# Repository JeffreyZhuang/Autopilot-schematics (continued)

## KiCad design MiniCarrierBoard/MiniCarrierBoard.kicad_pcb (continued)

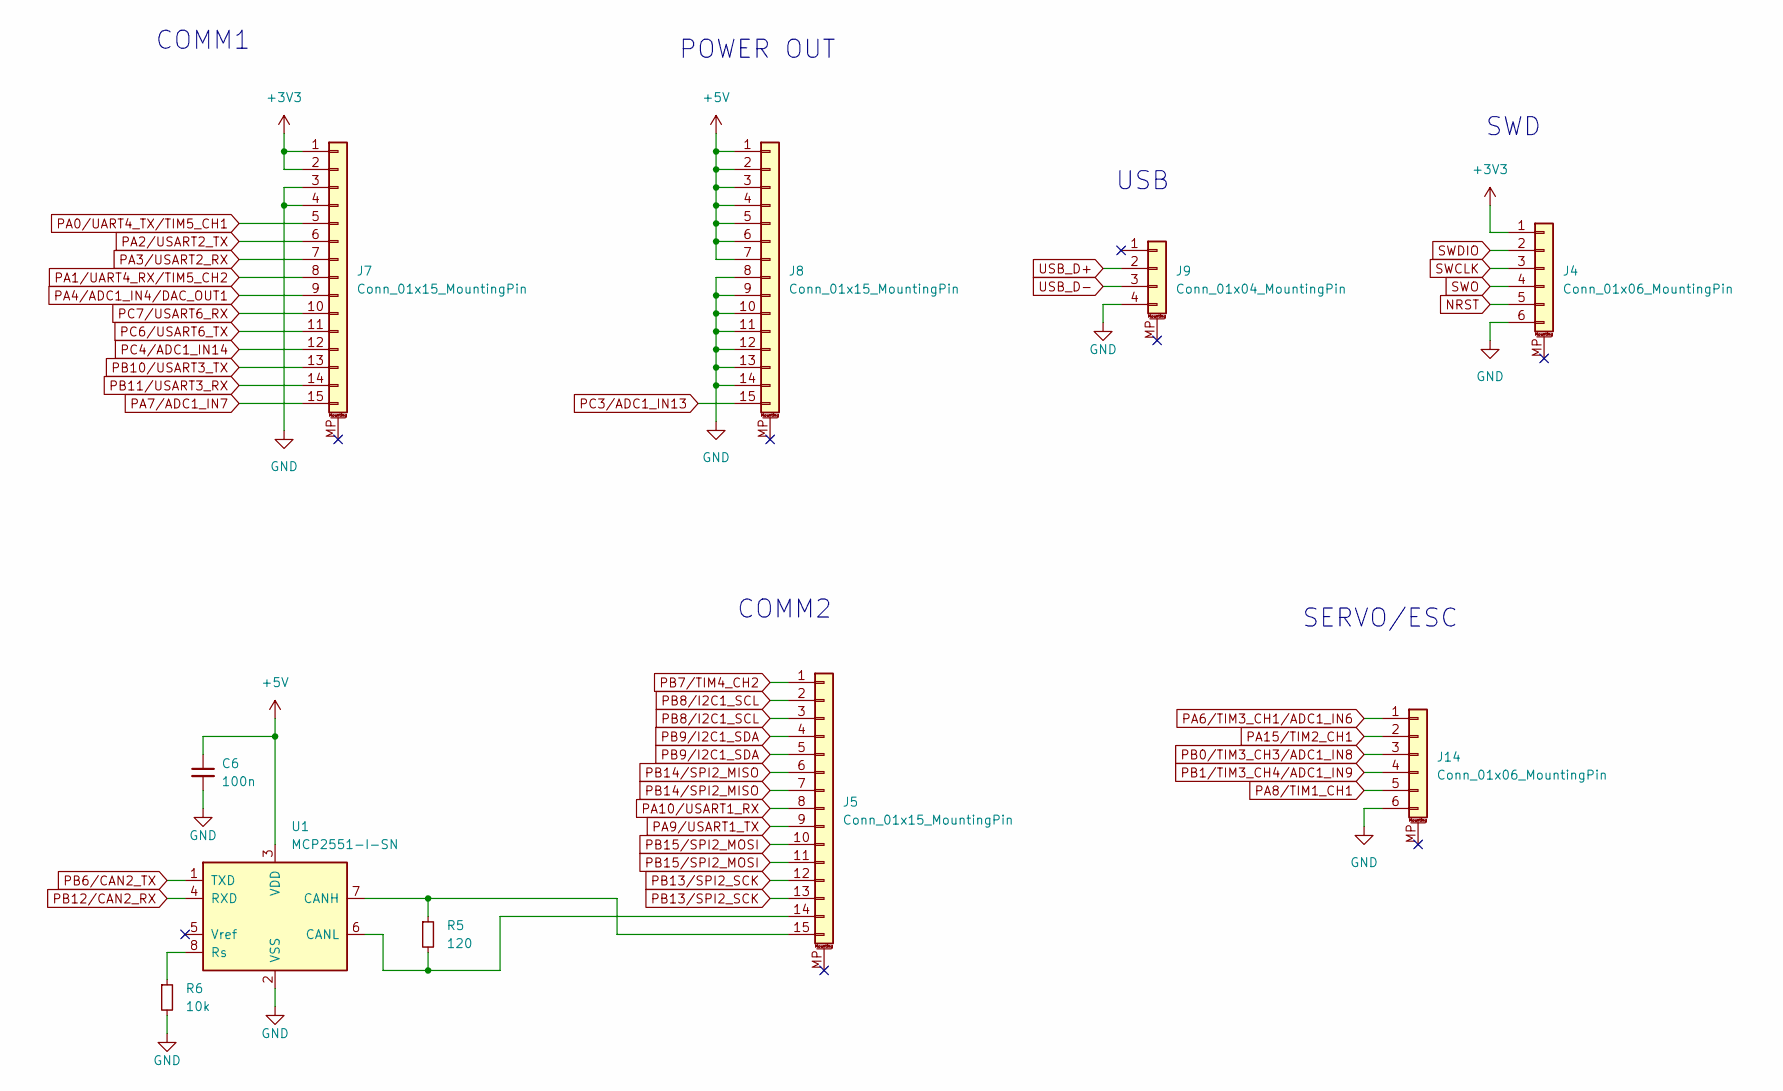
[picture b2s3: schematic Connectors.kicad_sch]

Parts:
C6: 100n; C_0402_1005Metric_Pad0.74x0.62mm_HandSolder; LCSC Part # N/A (C1525)
J4, J14: Conn_01x06_MountingPin; JST_GH_BM06B-GHS-TBT_1x06-1MP_P1.25mm_Vertical; LCSC Part # C189892
J5, J7, J8: Conn_01x15_MountingPin; JST_GH_BM15B-GHS-TBT_1x15-1MP_P1.25mm_Vertical; LCSC Part # C5305069
J9: Conn_01x04_MountingPin; JST_GH_BM04B-GHS-TBT_1x04-1MP_P1.25mm_Vertical; LCSC Part # C161692
R5: 120; R_0402_1005Metric_Pad0.72x0.64mm_HandSolder; LCSC Part # C25079
R6: 10k; R_0402_1005Metric_Pad0.72x0.64mm_HandSolder; LCSC Part # N/A (C25744)
U1: MCP2551-I-SN; SOIC-8_3.9x4.9mm_P1.27mm; LCSC Part # C49558

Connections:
+3V3: J4.1, J7.1, J7.2; also elsewhere on the board
+5V: C6.1, J8.1, J8.2, J8.3, J8.4, J8.5, J8.6, J8.7, U1.3 (VDD); also elsewhere on the board
GND: C6.2, J4.6, J7.3, J7.4, J8.8, J8.9, J8.10, J8.11, J8.12, J8.13, J8.14, J9.4, J14.6, R6.2, U1.2 (VSS); also elsewhere on the board
NRST: J4.5; also elsewhere on the board
unnamed: J5.14, R5.2, U1.6 (CANL)
unnamed: J5.15, R5.1, U1.7 (CANH)
unnamed: R6.1, U1.8 (Rs)
PA0/UART4_TX/TIM5_CH1: J7.5; also elsewhere on the board
PA1/UART4_RX/TIM5_CH2: J7.8; also elsewhere on the board
PA2/USART2_TX: J7.6; also elsewhere on the board
PA3/USART2_RX: J7.7; also elsewhere on the board
PA4/ADC1_IN4/DAC_OUT1: J7.9; also elsewhere on the board
PA6/TIM3_CH1/ADC1_IN6: J14.1; also elsewhere on the board
PA7/ADC1_IN7: J7.15; also elsewhere on the board
PA8/TIM1_CH1: J14.5; also elsewhere on the board
PA9/USART1_TX: J5.9; also elsewhere on the board
PA10/USART1_RX: J5.8; also elsewhere on the board
PA15/TIM2_CH1: J14.2; also elsewhere on the board
PB0/TIM3_CH3/ADC1_IN8: J14.3; also elsewhere on the board
PB1/TIM3_CH4/ADC1_IN9: J14.4; also elsewhere on the board
PB6/CAN2_TX: U1.1 (TXD); also elsewhere on the board
PB7/TIM4_CH2: J5.1; also elsewhere on the board
PB8/I2C1_SCL: J5.2, J5.3; also elsewhere on the board
PB9/I2C1_SDA: J5.4, J5.5; also elsewhere on the board
PB10/USART3_TX: J7.13; also elsewhere on the board
PB11/USART3_RX: J7.14; also elsewhere on the board
PB12/CAN2_RX: U1.4 (RXD); also elsewhere on the board
PB13/SPI2_SCK: J5.12, J5.13; also elsewhere on the board
PB14/SPI2_MISO: J5.6, J5.7; also elsewhere on the board
PB15/SPI2_MOSI: J5.10, J5.11; also elsewhere on the board
PC3/ADC1_IN13: J8.15; also elsewhere on the board
PC4/ADC1_IN14: J7.12; also elsewhere on the board
PC6/USART6_TX: J7.11; also elsewhere on the board
PC7/USART6_RX: J7.10; also elsewhere on the board
SWCLK: J4.3; also elsewhere on the board
SWDIO: J4.2; also elsewhere on the board
SWO: J4.4; also elsewhere on the board
USB_D+: J9.2; also elsewhere on the board
USB_D-: J9.3; also elsewhere on the board

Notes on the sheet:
POWER OUT
COMM1
SWD
USB
COMM2
SERVO/ESC

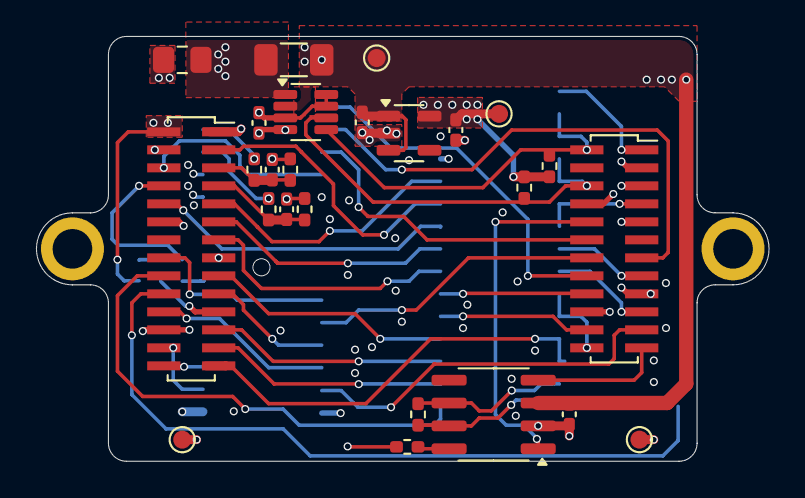
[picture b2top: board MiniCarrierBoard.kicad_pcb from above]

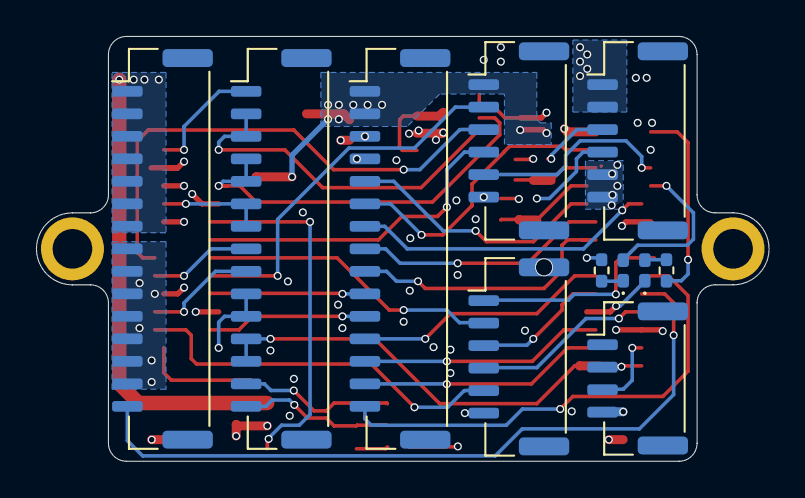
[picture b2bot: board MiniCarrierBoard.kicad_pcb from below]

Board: 4 copper layers, 40.7 x 23.6 mm, 38 parts (11 on the bottom side), 47 nets.

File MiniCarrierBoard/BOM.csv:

"Reference","Value","Footprint","Qty","LCSC Part #"
"C1,C2","1u","Capacitor_SMD:C_0402_1005Metric_Pad0.74x0.62mm_HandSolder","2","N/A (C2959727)"
"C3,C6,C9,C10","100n","Capacitor_SMD:C_0402_1005Metric_Pad0.74x0.62mm_HandSolder","4","N/A (C1525)"
"C5","10u","Capacitor_SMD:C_0805_2012Metric_Pad1.18x1.45mm_HandSolder","1","N/A (C15850)"
"D1","GREEN","LED_SMD:LED_0402_1005Metric_Pad0.77x0.64mm_HandSolder","1","C130723"
"D2","RED","LED_SMD:LED_0402_1005Metric_Pad0.77x0.64mm_HandSolder","1","N/A (C130719)"
"H1,H2","MountingHole_Pad","MountingHole:MountingHole_2.2mm_M2_ISO7380_Pad","2","N/A"
"J1","Conn_02x12_Odd_Even","Connector_PinSocket_1.00mm:PinSocket_2x12_P1.00mm_Vertical_SMD","1","N/A"
"J2","Conn_02x14_Odd_Even","Connector_PinSocket_1.00mm:PinSocket_2x14_P1.00mm_Vertical_SMD","1","N/A"
"J4,J6,J14","Conn_01x06_MountingPin","Connector_JST:JST_GH_BM06B-GHS-TBT_1x06-1MP_P1.25mm_Vertical","3","C189892"
"J5,J7,J8","Conn_01x15_MountingPin","Connector_JST:JST_GH_BM15B-GHS-TBT_1x15-1MP_P1.25mm_Vertical","3","C5305069"
"J9","Conn_01x04_MountingPin","Connector_JST:JST_GH_BM04B-GHS-TBT_1x04-1MP_P1.25mm_Vertical","1","C161692"
"R1,R2","1k","Resistor_SMD:R_0402_1005Metric_Pad0.72x0.64mm_HandSolder","2","N/A (C11702)"
"R3,R4","2k2","Resistor_SMD:R_0402_1005Metric_Pad0.72x0.64mm_HandSolder","2","N/A (C25879)"
"R5","120","Resistor_SMD:R_0402_1005Metric_Pad0.72x0.64mm_HandSolder","1","C25079"
"R6,R7,R8","10k","Resistor_SMD:R_0402_1005Metric_Pad0.72x0.64mm_HandSolder","3","N/A (C25744)"
"R9,R10","2M","Resistor_SMD:R_0402_1005Metric_Pad0.72x0.64mm_HandSolder","2","C138014"
"R11","10m 1W 1%","Resistor_SMD:R_1206_3216Metric_Pad1.30x1.75mm_HandSolder","1","C7467248"
"TP1,TP2,TP3,TP4","TestPoint","TestPoint:TestPoint_Pad_D1.0mm","4","N/A"
"U1","MCP2551-I-SN","Package_SO:SOIC-8_3.9x4.9mm_P1.27mm","1","C49558"
"U2","TLV70233_SOT23-5","Package_TO_SOT_SMD:SOT-23-5","1","C26833"
"U3","INA219AxDCN","Package_TO_SOT_SMD:SOT-23-8","1","C2155693"
